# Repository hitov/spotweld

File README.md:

# Tiny Spot Welder

This is the Kicad project of tiny spot welder board.

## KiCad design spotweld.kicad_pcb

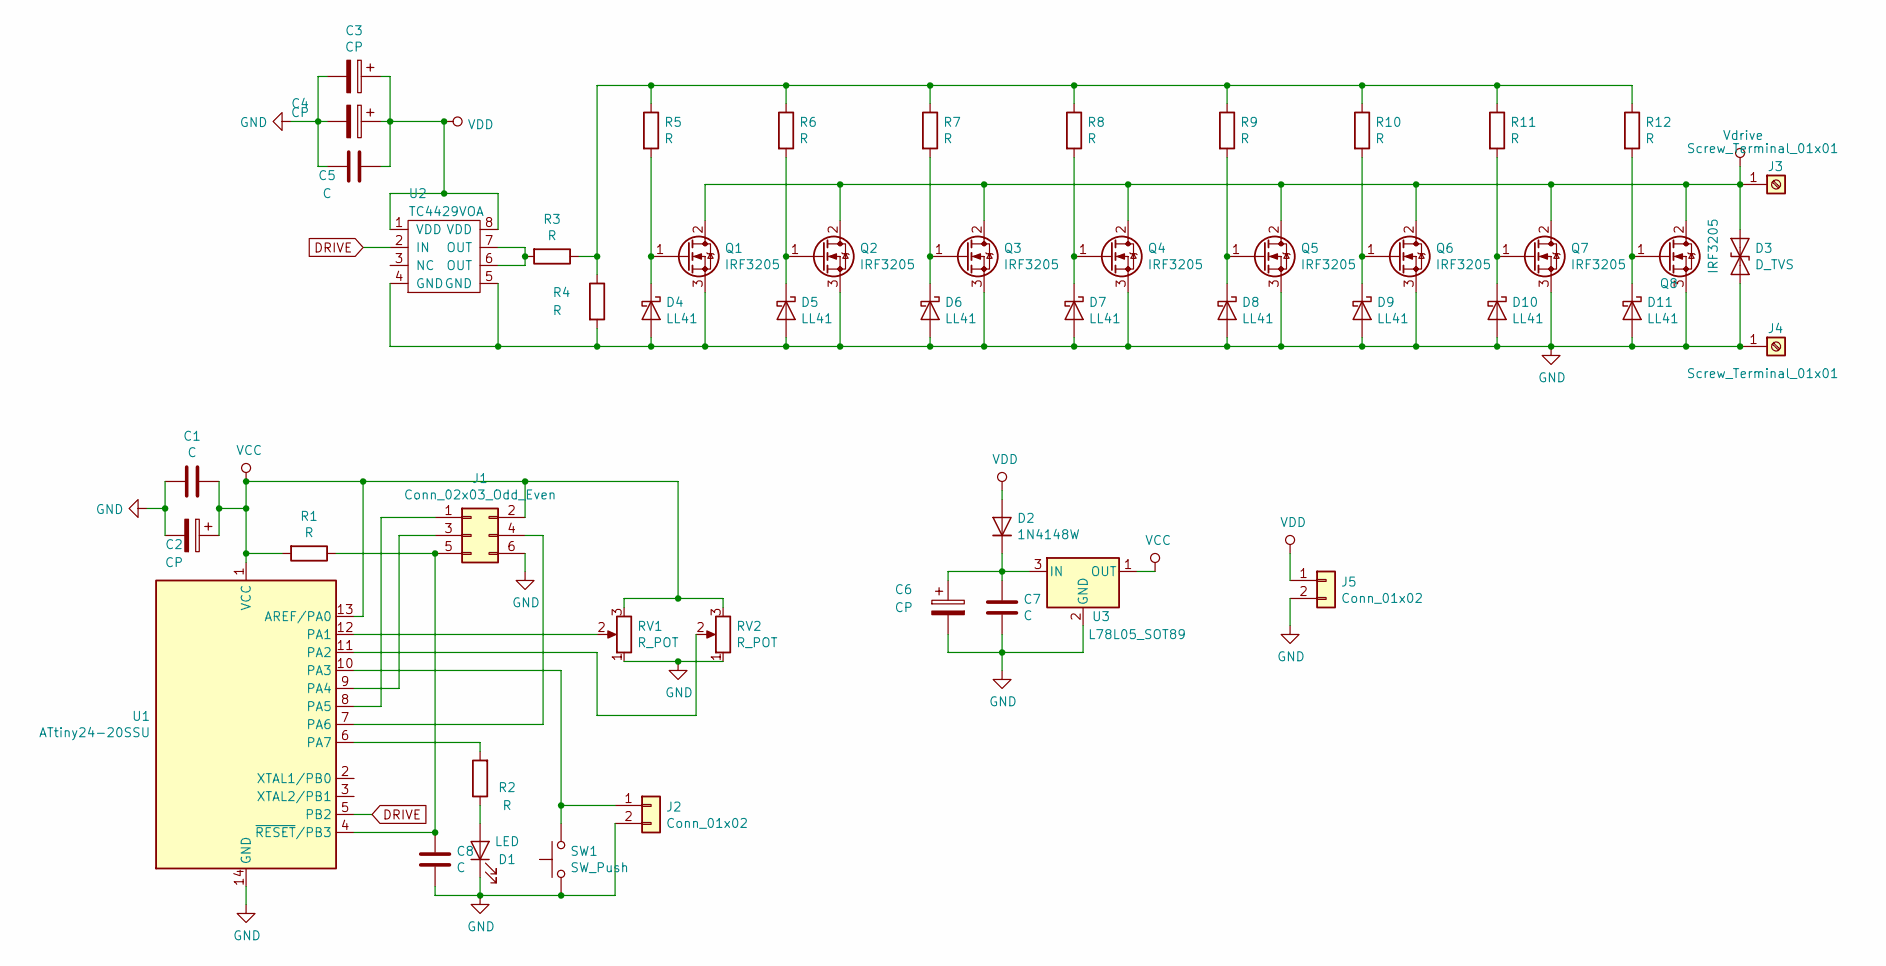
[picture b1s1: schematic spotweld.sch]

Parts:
C1, C5, C7, C8: C; C_0805_2012Metric
C2, C6: CP; CP_Radial_D6.3mm_P2.50mm
C3: CP; CP_Radial_D8.0mm_P3.50mm
C4: CP; C_1206_3216Metric
D1: LED; LED_0805_2012Metric
D2: 1N4148W; D_SOD-123
D3: D_TVS; D_MiniMELF
D4, D5, D6, D7, D8, D9, D10, D11: LL41; D_MiniMELF
J1: Conn_02x03_Odd_Even; PinHeader_2x03_P2.54mm_Vertical
J2, J5: Conn_01x02; PinHeader_1x02_P2.54mm_Vertical
J3, J4: Screw_Terminal_01x01
Q1, Q2, Q3, Q4, Q5, Q6, Q7, Q8: IRF3205; TO-220-3_Horizontal_TabDown
R1, R2, R3, R4, R5, R6, R7, R8, R9, R10, R11, R12: R; R_0805_2012Metric
RV1, RV2: R_POT; Potentiometer_Piher_T-16H_Single_Horizontal
SW1: SW_Push; SW_PUSH_6mm_H5mm
U1: ATtiny24-20SSU; SOIC-14_3.9x8.7mm_P1.27mm
U2: TC4429VOA; SOIC-8-1EP_3.9x4.9mm_P1.27mm_EP2.29x3mm
U3: L78L05_SOT89; SOT-89-3

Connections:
DRIVE: U1.5 (PB2), U2.2 (IN)
GND: C1.2, C2.2, C3.2, C4.2, C5.1, C6.2, C7.2, C8.2, D1.1 (K), D3.2 (A2), D4.2 (A), D5.2 (A), D6.2 (A), D7.2 (A), D8.2 (A), D9.2 (A), D10.2 (A), D11.2 (A), J1.6, J2.2, J4.1, J5.2, Q1.3 (S), Q2.3 (S), Q3.3 (S), Q4.3 (S), Q5.3 (S), Q6.3 (S), Q7.3 (S), Q8.3 (S), R4.2, RV1.1, RV2.1, SW1.1, U1.14 (GND), U2.4 (GND), U2.5 (GND), U3.2 (GND)
unnamed: C6.1, C7.1, D2.1 (K), U3.3 (IN)
unnamed: C8.1, J1.5, R1.1, U1.4 (~RESET~/PB3)
unnamed: D1.2 (A), R2.1
unnamed: D4.1 (K), Q1.1 (G), R5.2
unnamed: D5.1 (K), Q2.1 (G), R6.2
unnamed: D6.1 (K), Q3.1 (G), R7.2
unnamed: D7.1 (K), Q4.1 (G), R8.2
unnamed: D8.1 (K), Q5.1 (G), R9.2
unnamed: D9.1 (K), Q6.1 (G), R10.2
unnamed: D10.1 (K), Q7.1 (G), R11.2
unnamed: D11.1 (K), Q8.1 (G), R12.2
unnamed: J1.1, U1.8 (PA5)
unnamed: J1.3, U1.9 (PA4)
unnamed: J1.4, U1.7 (PA6)
unnamed: J2.1, SW1.2, U1.10 (PA3)
unnamed: R2.2, U1.6 (PA7)
unnamed: R3.2, U2.6 (OUT), U2.7 (OUT)
unnamed: R3.1, R4.1, R5.1, R6.1, R7.1, R8.1, R9.1, R10.1, R11.1, R12.1
unnamed: RV1.2, U1.12 (PA1)
unnamed: RV2.2, U1.11 (PA2)
VCC: C1.1, C2.1, J1.2, R1.2, RV1.3, RV2.3, U1.1 (VCC), U1.13 (AREF/PA0), U3.1 (OUT)
VDD: C3.1, C4.1, C5.2, D2.2 (A), J5.1, U2.1 (VDD), U2.8 (VDD)
Vdrive: D3.1 (A1), J3.1, Q1.2 (D), Q2.2 (D), Q3.2 (D), Q4.2 (D), Q5.2 (D), Q6.2 (D), Q7.2 (D), Q8.2 (D)

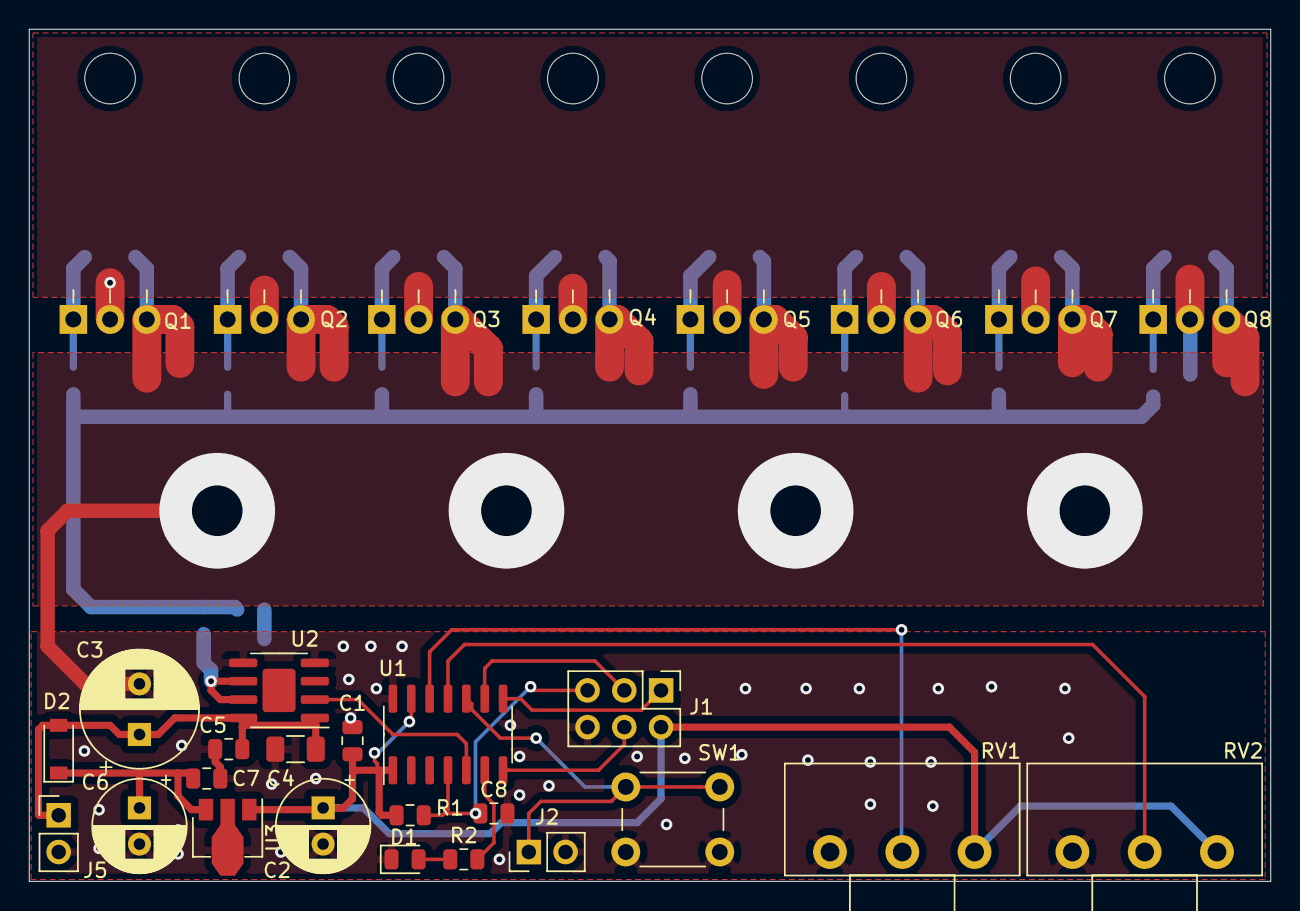
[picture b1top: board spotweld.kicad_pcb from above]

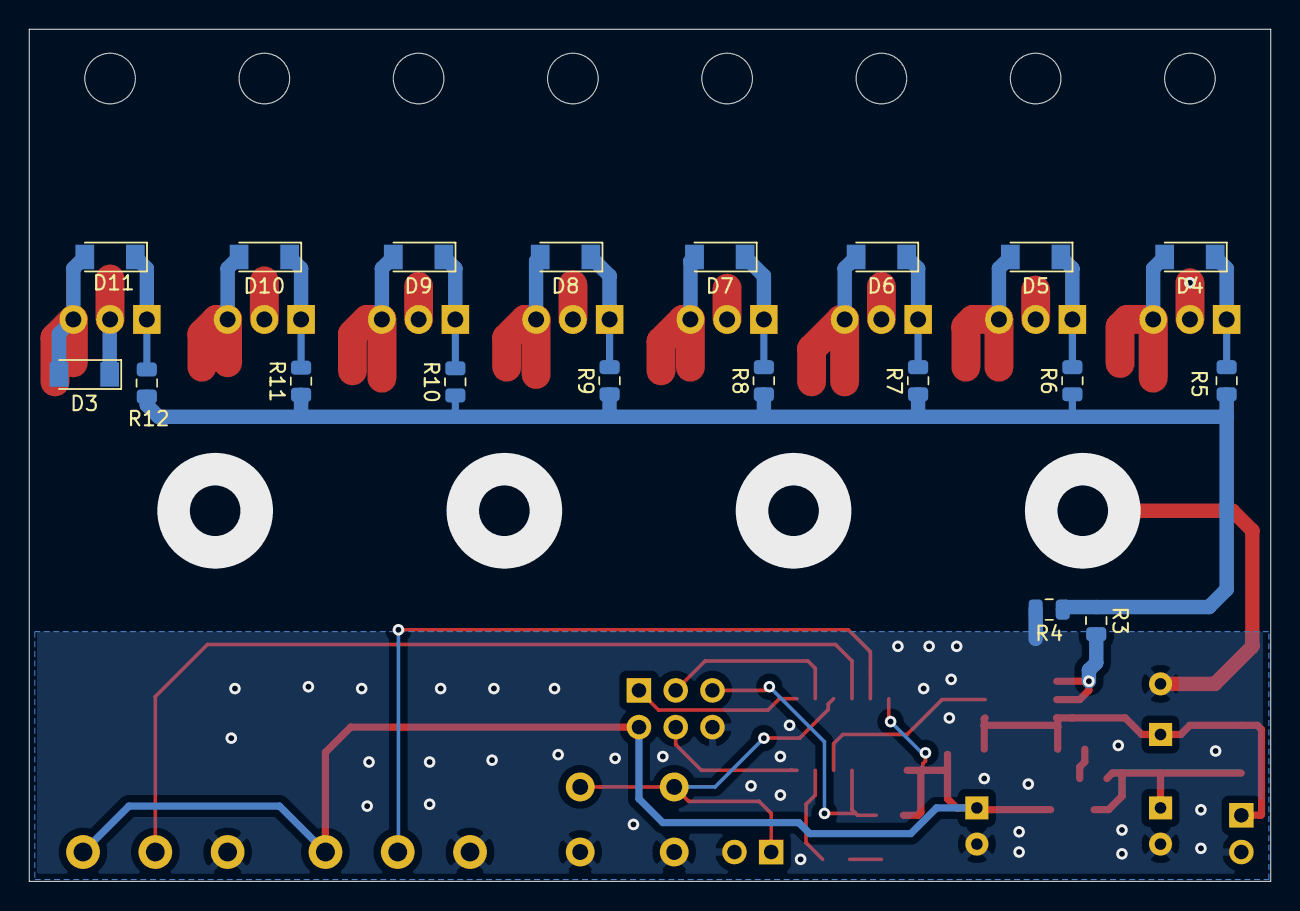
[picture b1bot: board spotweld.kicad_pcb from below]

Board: 2 copper layers, 85.9 x 58.9 mm, 48 parts (19 on the bottom side), 25 nets.

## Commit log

2019-09-18 Spot welder - initial commit
2019-09-18 Export manufacture files
2019-09-18 Correct via clearence
2019-10-22 Update schematics component values
2019-10-22 Include gerber files
    Prototype boards are fabricated with those
2019-10-22 Update readme file
2019-10-22 Update schematics pdf
